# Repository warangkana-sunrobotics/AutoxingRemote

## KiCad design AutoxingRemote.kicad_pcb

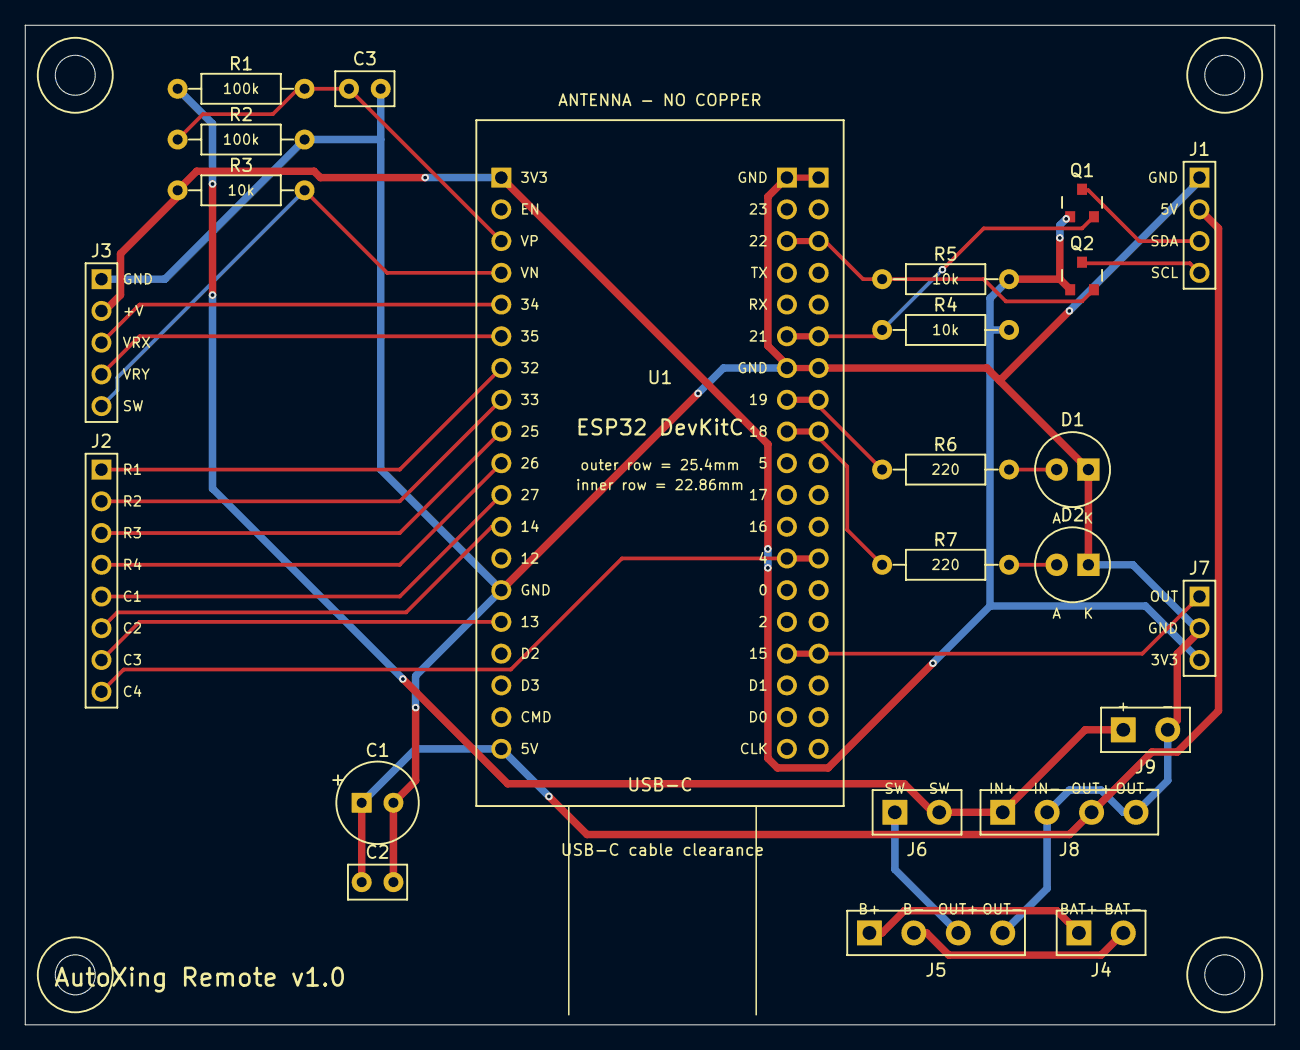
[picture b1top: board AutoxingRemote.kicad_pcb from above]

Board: 2 copper layers, 100.0 x 80.0 mm, 28 parts (0 on the bottom side), 28 nets.

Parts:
C1: 100u; CP_Radial_D6.3mm_P2.54mm
C2, C3: 100n; C_Disc_P2.54mm
D1: GREEN; LED_D5.0mm
D2: RED; LED_D5.0mm
H1, H2, H3, H4: M3; MountingHole_3.2mm_M3
J1: LCD1602_I2C; PinHeader_1x4_P2.54mm
J2: Keypad4x4; PinHeader_1x8_P2.54mm
J3: Joystick; PinHeader_1x5_P2.54mm
J4: 18650; WirePad_1x2_P3.5mm
J5: TP4056; WirePad_1x4_P3.5mm
J6: SW DS-428; WirePad_1x2_P3.5mm
J7: IR_Receiver; PinHeader_1x3_P2.54mm
J8: MT3608 5V; WirePad_1x4_P3.5mm
J9: BattLevel; WirePad_1x2_P3.5mm
Q1, Q2: BSS138; SOT-23
R1, R2: 100k; R_Axial_P10.16mm
R3, R4, R5: 10k; R_Axial_P10.16mm
R6, R7: 220; R_Axial_P10.16mm
U1: ESP32-DevKitC-WROVER 38P; ESP32_DevKitC_38P_2row

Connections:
3V3: J3.2, J7.3, Q1.1, Q2.1, R3.1, R4.2, R5.2, U1.1
+5V: C1.1, C2.1, J1.2, J8.3, U1.19
BAT+: J4.1, J5.1
BAT-: J4.2, J5.2
GND: C1.2, C2.2, C3.2, D1.1, D2.1, J1.1, J3.1, J5.4, J7.2, J8.2, J8.4, J9.2, R2.2, U1.14, U1.20, U1.26
IR: J7.1, U1.35
JOY_SW: J3.5, R3.2, U1.4
JOY_X: J3.3, U1.5
JOY_Y: J3.4, U1.6
KP_C1: J2.5, U1.11
KP_C2: J2.6, U1.12
KP_C3: J2.7, U1.15
KP_C4: J2.8, U1.32
KP_R1: J2.1, U1.7
KP_R2: J2.2, U1.8
KP_R3: J2.3, U1.9
KP_R4: J2.4, U1.10
LED_G: R6.1, U1.27
LED_GA: D1.2, R6.2
LED_R: R7.1, U1.28
LED_RA: D2.2, R7.2
SCL: Q2.2, R5.1, U1.22
SCL5: J1.4, Q2.3
SDA: Q1.2, R4.1, U1.25
SDA5: J1.3, Q1.3
TP_OUT: J5.3, J6.1
VBAT_S: C3.1, R1.2, R2.1, U1.3
VSW: J6.2, J8.1, J9.1, R1.1

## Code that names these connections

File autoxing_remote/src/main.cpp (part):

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// --- ขาของบอร์ด AutoXing Remote PCB rev 1.0 (ดู AutoxingRemote_schematic_full.pdf) ---
const int PIN_I2C_SDA = 21;     // LCD SDA ผ่าน level shifter Q1
const int PIN_I2C_SCL = 22;     // LCD SCL ผ่าน level shifter Q2
const int PIN_JOY_X = 34;       // Joystick VRX (ADC1)
const int PIN_JOY_Y = 35;       // Joystick VRY (ADC1)
const int PIN_JOY_SW = 39;      // Joystick SW, active LOW, pull-up R3 บนบอร์ด
const int PIN_LED_GREEN = 19;   // D1
const int PIN_LED_RED = 18;     // D2
const int PIN_VBAT = 36;        // VBAT/2 จาก R1/R2 (ADC1)
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void calibrateJoystick() {
  long sumX = 0, sumY = 0;
  for (int i = 0; i < 32; ++i) {
    sumX += analogRead(PIN_JOY_X);
    sumY += analogRead(PIN_JOY_Y);
    delay(2);
  }
  joyCenterX = sumX / 32;
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  lastRead = millis();

  // GPIO39 อาจมี glitch สั้น ๆ ตอน WiFi/ADC ทำงาน จึงต้องอ่าน LOW ติดกัน 2 ครั้งก่อน
  if (digitalRead(PIN_JOY_SW) == LOW) {
    if (lowCount < 2) ++lowCount;
  } else {
    lowCount = 0;
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    return;
  }

  float x = joystickAxis(analogRead(PIN_JOY_X), joyCenterX);
  float y = joystickAxis(analogRead(PIN_JOY_Y), joyCenterY);
  if (JOY_INVERT_X) x = -x;
  if (JOY_INVERT_Y) y = -y;
  bool deflected = x != 0.0f || y != 0.0f;
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  pinMode(PIN_LED_GREEN, OUTPUT);
  pinMode(PIN_LED_RED, OUTPUT);
  digitalWrite(PIN_LED_RED, HIGH);         // แดงติดระหว่างบูต/ต่อ Wi-Fi
  pinMode(PIN_JOY_SW, INPUT);              // GPIO39 ไม่มี pull-up ภายใน (มี R3 บนบอร์ด)
  analogSetPinAttenuation(PIN_JOY_X, ADC_11db);
  analogSetPinAttenuation(PIN_JOY_Y, ADC_11db);
  analogSetPinAttenuation(PIN_VBAT, ADC_11db);
  initLcd();
  lcdWriteLine(0, "AutoXing Remote");
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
